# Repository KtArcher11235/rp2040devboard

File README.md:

# rp2040devboard
a signature devboard based on the rp2040 designed to be as minimal as possible, allowing for expandability through the pins.

## specs
- rp2040
- 16 MiB Flash
- LED on gipo25
- 12 MHz crystal
- USB interface with voltage regulator

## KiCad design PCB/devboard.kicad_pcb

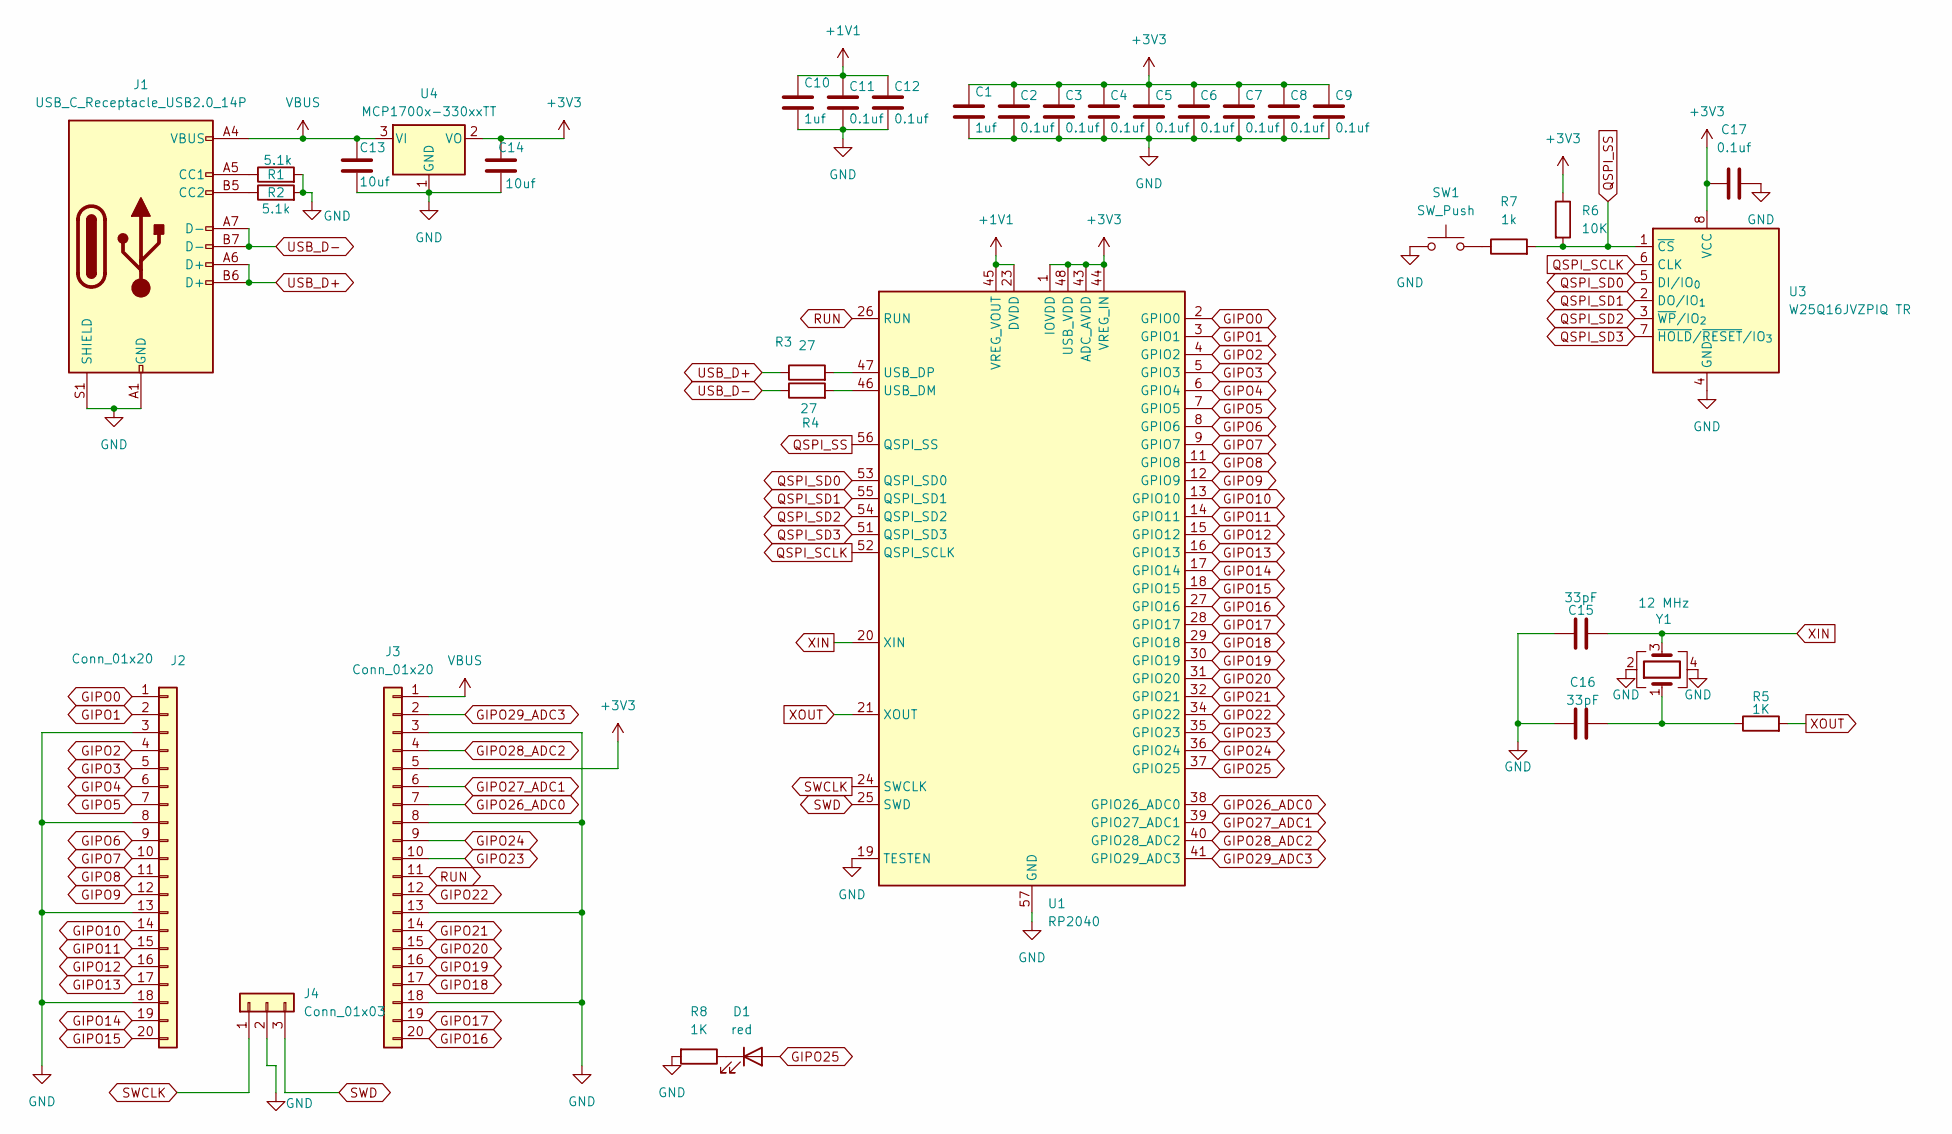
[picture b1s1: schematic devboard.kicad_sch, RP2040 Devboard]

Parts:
C1, C10: 1uf; C_0402_1005Metric
C2, C3, C4, C5, C6, C7, C8, C9, C11, C12, C17: 0.1uf; C_0402_1005Metric
C13, C14: 10uf; C_0603_1608Metric
C15, C16: 33pF; C_0402_1005Metric
D1: red; LED_0402_1005Metric
J1: USB_C_Receptacle_USB2.0_14P; USB_C_Receptacle_HRO_TYPE-C-31-M-12
J2, J3: Conn_01x20; PinHeader_1x20_P2.54mm_Vertical
J4: Conn_01x03; PinHeader_1x03_P2.54mm_Vertical
R1, R2: 5.1k; R_0402_1005Metric
R3, R4: 27; R_0402_1005Metric
R5, R8: 1K; R_0402_1005Metric
R6: 10K; R_0402_1005Metric
R7: 1k; R_0402_1005Metric
SW1: SW_Push; SW_Push_SPST_NO_Alps_SKRK
U1: RP2040; QFN-56-1EP_7x7mm_P0.4mm_EP3.2x3.2mm
U3: W25Q16JVZPIQ TR; Winbond_USON-8-1EP_3x2mm_P0.5mm_EP0.2x1.6mm
U4: MCP1700x-330xxTT; SOT-23
Y1: 12 MHz; Crystal_SMD_3225-4Pin_3.2x2.5mm

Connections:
+1V1: C10.1, C11.1, C12.1, U1.23 (DVDD), U1.45 (VREG_VOUT), U1.50 (DVDD)
+3V3: C1.1, C2.1, C3.1, C4.1, C5.1, C6.1, C7.1, C8.1, C9.1, C14.1, C17.1, J3.5 (Pin_16), R6.1, U1.1 (IOVDD), U1.10 (IOVDD), U1.22 (IOVDD), U1.33 (IOVDD), U1.42 (IOVDD), U1.43 (ADC_AVDD), U1.44 (VREG_IN), U1.48 (USB_VDD), U1.49 (IOVDD), U3.8 (VCC), U4.2 (VO)
GIPO0: J2.1, U1.2 (GPIO0)
GIPO1: J2.2, U1.3 (GPIO1)
GIPO2: J2.4, U1.4 (GPIO2)
GIPO3: J2.5, U1.5 (GPIO3)
GIPO4: J2.6, U1.6 (GPIO4)
GIPO5: J2.7, U1.7 (GPIO5)
GIPO6: J2.9, U1.8 (GPIO6)
GIPO7: J2.10, U1.9 (GPIO7)
GIPO8: J2.11, U1.11 (GPIO8)
GIPO9: J2.12, U1.12 (GPIO9)
GIPO10: J2.14, U1.13 (GPIO10)
GIPO11: J2.15, U1.14 (GPIO11)
GIPO12: J2.16, U1.15 (GPIO12)
GIPO13: J2.17, U1.16 (GPIO13)
GIPO14: J2.19, U1.17 (GPIO14)
GIPO15: J2.20, U1.18 (GPIO15)
GIPO16: J3.20 (Pin_1), U1.27 (GPIO16)
GIPO17: J3.19 (Pin_2), U1.28 (GPIO17)
GIPO18: J3.17 (Pin_4), U1.29 (GPIO18)
GIPO19: J3.16 (Pin_5), U1.30 (GPIO19)
GIPO20: J3.15 (Pin_6), U1.31 (GPIO20)
GIPO21: J3.14 (Pin_7), U1.32 (GPIO21)
GIPO22: J3.12 (Pin_9), U1.34 (GPIO22)
GIPO23: J3.10 (Pin_11), U1.35 (GPIO23)
GIPO24: J3.9 (Pin_12), U1.36 (GPIO24)
GIPO25: D1.2 (A), U1.37 (GPIO25)
GIPO26_ADC0: J3.7 (Pin_14), U1.38 (GPIO26_ADC0)
GIPO27_ADC1: J3.6 (Pin_15), U1.39 (GPIO27_ADC1)
GIPO28_ADC2: J3.4 (Pin_17), U1.40 (GPIO28_ADC2)
GIPO29_ADC3: J3.2 (Pin_19), U1.41 (GPIO29_ADC3)
GND: C1.2, C2.2, C3.2, C4.2, C5.2, C6.2, C7.2, C8.2, C9.2, C10.2, C11.2, C12.2, C13.2, C14.2, C15.1, C16.1, C17.2, J1.A1 (GND), J1.A12 (GND), J1.B1 (GND), J1.B12 (GND), J1.S1 (SHIELD), J2.3, J2.8, J2.13, J2.18, J3.3 (Pin_18), J3.8 (Pin_13), J3.13 (Pin_8), J3.18 (Pin_3), J4.2, R1.2, R2.2, R8.2, SW1.1, U1.19 (TESTEN), U1.57 (GND), U3.4 (GND), U4.1 (GND), Y1.2, Y1.4
unnamed: C16.2, R5.1, Y1.1
unnamed: D1.1 (K), R8.1
unnamed: J1.A5 (CC1), R1.1
unnamed: J1.B5 (CC2), R2.1
unnamed: R7.1, SW1.2
unnamed: R4.2, U1.46 (USB_DM)
unnamed: R3.2, U1.47 (USB_DP)
QSPI_SCLK: U1.52 (QSPI_SCLK), U3.6 (CLK)
QSPI_SD0: U1.53 (QSPI_SD0), U3.5 (DI/IO_{0})
QSPI_SD1: U1.55 (QSPI_SD1), U3.2 (DO/IO_{1})
QSPI_SD2: U1.54 (QSPI_SD2), U3.3 (~WP/IO_{2})
QSPI_SD3: U1.51 (QSPI_SD3), U3.7 (~HOLD/~RESET/IO_{3})
QSPI_SS: R6.2, R7.2, U1.56 (QSPI_SS), U3.1 (~CS)
RUN: J3.11 (Pin_10), U1.26 (RUN)
SWCLK: J4.1, U1.24 (SWCLK)
SWD: J4.3, U1.25 (SWD)
USB_D+: J1.A6 (D+), J1.B6 (D+), R3.1
USB_D-: J1.A7 (D-), J1.B7 (D-), R4.1
VBUS: C13.1, J1.A4 (VBUS), J1.A9 (VBUS), J1.B4 (VBUS), J1.B9 (VBUS), J3.1 (Pin_20), U4.3 (VI)
XIN: C15.2, U1.20 (XIN), Y1.3
XOUT: R5.2, U1.21 (XOUT)

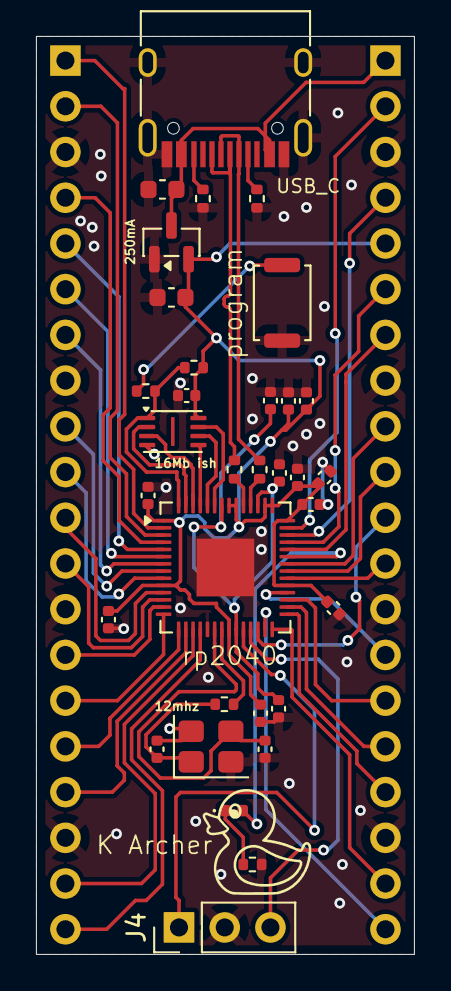
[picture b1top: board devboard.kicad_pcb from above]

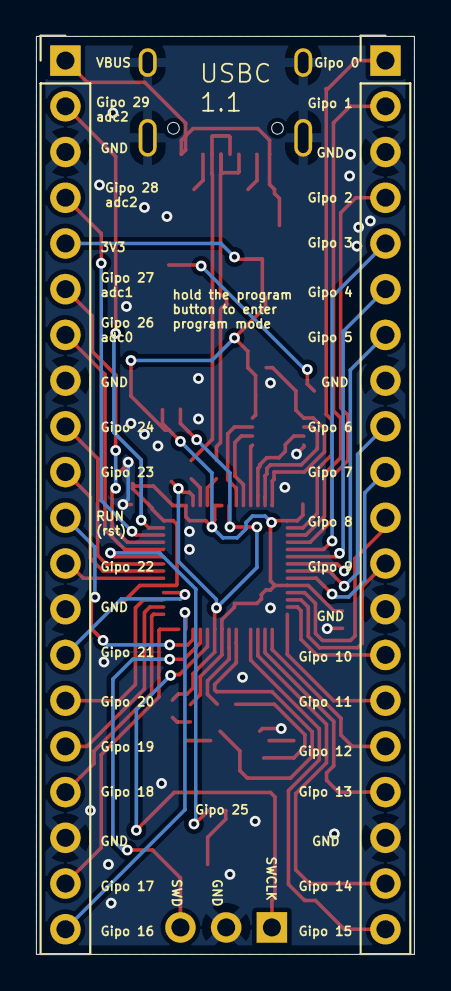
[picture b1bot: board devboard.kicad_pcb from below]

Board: 2 copper layers, 21.0 x 51.0 mm, 35 parts (2 on the bottom side), 54 nets.

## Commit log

2025-11-24 Add initial devboard CAD, PCB, and firmware files
    Added STEP model, KiCad PCB, schematic, project, and WRL files for the devboard hardware. Included a firmware Python file, gerber outputs, and a screenshot. Updated README.md to reflect new files.
2025-11-24 Add image to README for visual reference
    Added an image to enhance the README documentation.
2025-11-24 Update README with additional board specifications
    Added specifications for Flash, LED, and crystal.
2025-11-24 Fix formatting of hardware specifications in README
2025-11-24 Add specs section to README
    Added specifications section to README.
2025-11-24 Update README with additional specs
